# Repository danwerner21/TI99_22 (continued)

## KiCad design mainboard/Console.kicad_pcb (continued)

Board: 2 copper layers, 303 parts (0 on the bottom side), 325 nets, no tracks yet.

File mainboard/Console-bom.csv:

Qty|Reference(s)|Part|Type
---|------------|----|----
30|C1, C9, C11, C57, C63, C70, C71, C72, C73, C74, C75, C76, C77, C78, C80, C81, C82, C84, C85, C86, C87, C88, C89, C90, C91, C92, C93, C94, C95, C96|0.001uF|Capacitor
1|C2|22pF|Capacitor
3|C3, C5, C58|22uF electroyltic|Electrolytic Capacitor
38|C4, C7, C13, C14, C19, C22, C23, C24, C25, C26, C27, C28, C29, C30, C31, C32, C33, C34, C35, C36, C37, C38, C39, C40, C41, C42, C43, C44, C45, C46, C47, C48, C49, C50, C53, C54, C66, C69|0.1uF|Capacitor
1|C6|1uF|Capacitor
8|C8, C12, C51, C62, C64, C65, C79, C83|0.01uF|Capacitor
1|C10|100uF|Capacitor
6|C15, C16, C17, C18, C20, C21,C52,C59|100uF electrolytic|Electrolytic Capacitor
1|C55|12pF|Capacitor
1|C56|56pF|Capacitor
1|C60|220uF electrolytic|Electrolytic Capacitor
1|C61|0.1uF|Capacitor
1|C67|220pF|Capacitor
1|C68|0.022uF|Capacitor
2|CR1, CR4|1N4148|Diode
2|CR2, CR3|1N914B|Diode
1|D1|LED|LED
1|J1|Pin Header 01x02 Male|Pin Header 01x02 Male
1|J2|Pin Header 01x02 Male|Pin Header 01x02 Male
1|J3|Screw Terminal 1x4|Screw Terminal 1x4
1|J4|Pin Header 01x16 Male|Pin Header 01x16 Male
2|J5, J6|Pin Header 01x02 Male|Pin Header 01x02 Male
1|J7|Pin Header 01x02 Male|Pin Header 01x02 Male
1|J8|Pin Header 01x02 Male|Pin Header 01x02 Male
1|J9|DB9 Connector Right Angle Male|DB9 Connector Right Angle Male
1|J10|DB9 Connector Right Angle Male|DB9 Connector Right Angle Male
1|J11|Pin Header 01x18 Male|Pin Header 01x18 Male
1|J12|Pin Header 2x22 Male|Pin Header 2x22 Male
1|J14|36 Pin Edge Connector|CONN EDGE DUAL FMALE 36POS 0.100 spacing
1|J15|Pin Header 02x18 Male|Pin Header 02x18 Male
1|J16|Pin Header 01x03 Male|Pin Header 01x03 Male
1|J17|Pin Header 01x03 Male|Pin Header 01x03 Male
1|L1|0.33uH Inductor|Inductor
9|L2, L3, L4, L12, L13, L14, L15, L16, L17|6.8uH  Inductor|Inductor
4|L5, L6, L7, L11|6.8uH  Inductor|Inductor
1|L8|2- 4.5uH  Inductor|Variable Inductor
1|L9|5.8uH  Inductor|Inductor
1|L10, L18, L19, L20, L21|INDUCTOR (BEAD)|Ferrite Bead
8|Q1, Q3, Q4, Q5, Q6, Q7, Q8, Q9|TIS92 Transistor|Transistor
1|Q2|2N3904  Transistor|Transistor
1|R1|150kohm|Resistor
11|R2, R9, R11, R18, R51, R52, R53, R54, R55, R56, R89|1kohm|Resistor
1|R3|12kohm|Resistor
1|R4|47kohm|Resistor
4|R5, R6, R7, R8|22ohm|Resistor
5|R10, R26, R88, R95, R96|4.7kohm|Resistor
5|R12, R13, R14, R15, R16|1Kohm|Resistor
3|R17, R91, R93|2.2kohm|Resistor
11|R19, R30, R63, R65, R67, R69, R71, R75, R77, R79, R82|470ohm|Resistor
1|R20|270ohm|Resistor
1|R21|1.5kohm|Resistor Network 9 pin
1|R22|361ohm|Resistor
4|R23, R35, R60, R81|5.6kohm|Resistor
4|R24, R27, R80, R83|10ohm|Resistor
1|R25|150ohm|Resistor
1|R28|470kohm|Resistor
1|R29|0ohm|Resistor
2|R31, R33|75ohm|Resistor
1|R32|470ohm|Resistor
11|R34, R40, R41, R42, R43, R44, R45, R46, R47, R48, R100|10kohm|Resistor
2|R36, R58|6.8kohm|Resistor
1|R37|2.2kohm|Resistor
1|R38|200ohm|Resistor
1|R39|120kohm|Resistor
1|R49|39kohm|Resistor
1|R50|6.8kohm|Resistor
1|R57|12kohm|Resistor
1|R59|15ohm|Resistor
2|R61, R62|10kohm|Resistor
2|R64, R72|1kohm|Resistor
2|R66, R76|1.5kohm|Resistor
2|R68, R78|270ohm|Resistor
1|R70|9.1kohm|Resistor
2|R73, R74|220ohm|Resistor
4|R84, R85, R86, R87|62ohm|Resistor
1|R90|3.3kohm|Resistor
4|R92, R94, R97, R99|100ohm|Resistor
1|R98|330ohm|Resistor
1|SW1|Dip Switch 6 pos|Dip Switch 6 pos
1|SW2|Pin Header 01x02 Male|Pin Header 01x02 Male
1|U1|TIM9904|IC
1|U2|TMS9900|IC
4|U3, U15, U20, U21|74LS04|IC
2|U4, U9|74LS32|IC
2|U5, U8|74LS138|IC
1|U6|74LS03|IC
1|U7|74LS08|IC
3|U10, U14, U18|74LS00|IC
2|U11, U40|74LS244|IC
1|U12|74LS373|IC
1|U13|74LS245|IC
1|U16|74LS74|IC
1|U17|74LS194|IC
1|U19|LM7905_TO220|IC
3|U22, U23, U24|TMC0430|IC (optional, replaced by Unicorn Board only known source is from TI/994a console)
3|U25, U26, U33|HM62256BLP|IC
2|U27, U28|27C64|IC
1|U29|SN76489|IC
1|U30|TMS9918|IC
3|U31, U32, U34|74LS574|IC
1|U35|TMS9901|IC
1|U36|RC4558|IC
1|U37|74LS156|IC
2|U38, U39|TIL119|IC
2|U41, U42|74LS367|IC
1|U43|74LS379|IC
1|U44|27C010|IC
1|Y1|48.000 MHz Crystal|Crystal
1|Y2|10.7MHz Crystal|Crystal

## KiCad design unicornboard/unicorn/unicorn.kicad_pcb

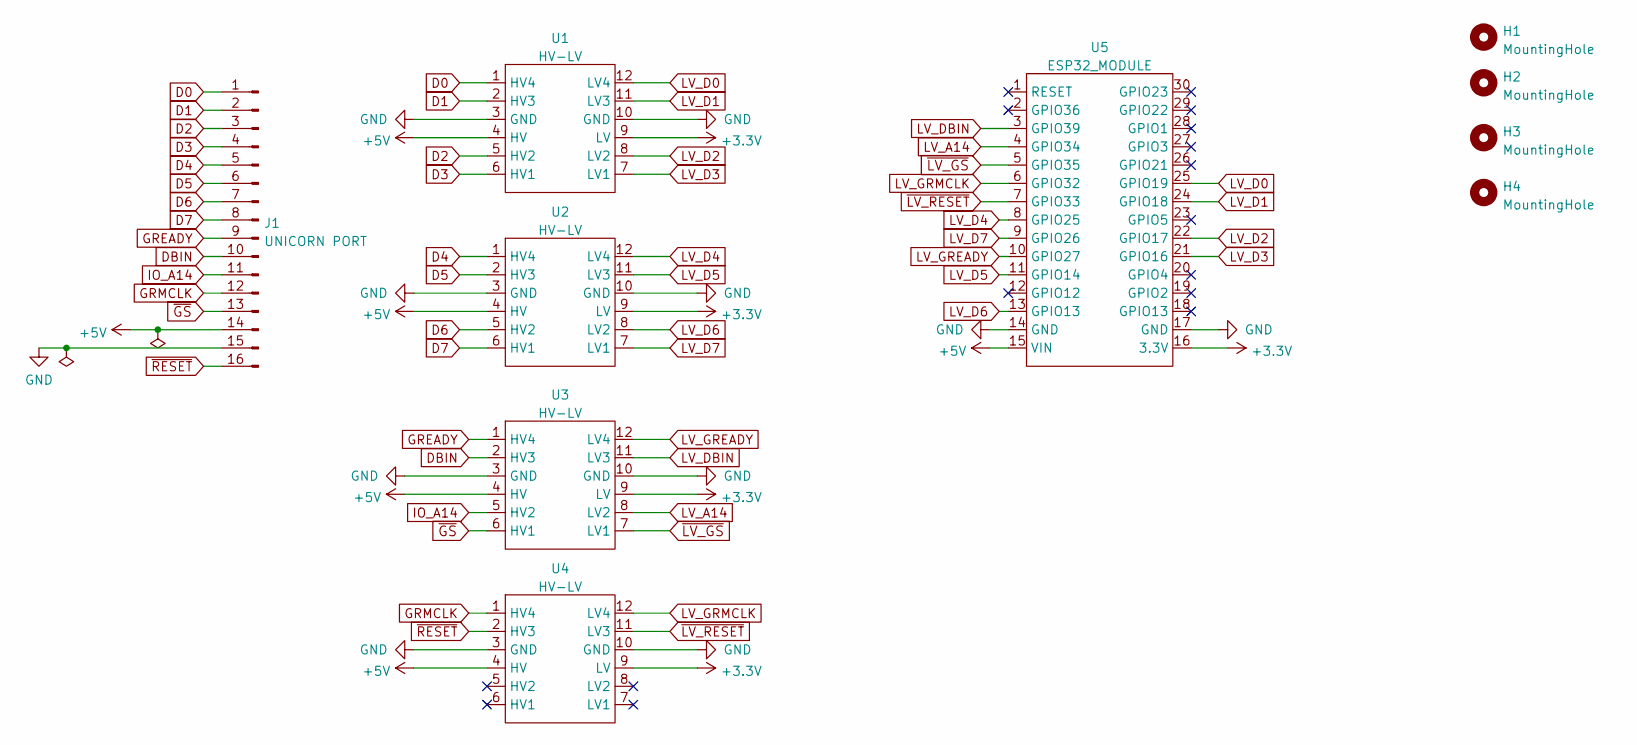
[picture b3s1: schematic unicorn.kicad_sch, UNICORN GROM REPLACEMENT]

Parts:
H1, H2, H3, H4: MountingHole; MountingHole_3.2mm_M3
J1: UNICORN PORT; PinHeader_1x16_P2.54mm_Vertical
U1, U2, U3, U4: HV-LV
U5: ESP32_MODULE; ESP32_DEVKIT_30

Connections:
+3.3V: U1.9 (LV), U2.9 (LV), U3.9 (LV), U4.9 (LV), U5.16 (3.3V)
+5V: J1.14, U1.4 (HV), U2.4 (HV), U3.4 (HV), U4.4 (HV), U5.15 (VIN)
D0: J1.1, U1.1 (HV4)
D1: J1.2, U1.2 (HV3)
D2: J1.3, U1.5 (HV2)
D3: J1.4, U1.6 (HV1)
D4: J1.5, U2.1 (HV4)
D5: J1.6, U2.2 (HV3)
D6: J1.7, U2.5 (HV2)
D7: J1.8, U2.6 (HV1)
DBIN: J1.10, U3.2 (HV3)
GND: J1.15, U1.3 (GND), U1.10 (GND), U2.3 (GND), U2.10 (GND), U3.3 (GND), U3.10 (GND), U4.3 (GND), U4.10 (GND), U5.14 (GND), U5.17 (GND)
GREADY: J1.9, U3.1 (HV4)
GRMCLK: J1.12, U4.1 (HV4)
IO_A14: J1.11, U3.5 (HV2)
LV_A14: U3.8 (LV2), U5.4 (GPIO34)
LV_D0: U1.12 (LV4), U5.25 (GPIO19)
LV_D1: U1.11 (LV3), U5.24 (GPIO18)
LV_D2: U1.8 (LV2), U5.22 (GPIO17)
LV_D3: U1.7 (LV1), U5.21 (GPIO16)
LV_D4: U2.12 (LV4), U5.8 (GPIO25)
LV_D5: U2.11 (LV3), U5.11 (GPIO14)
LV_D6: U2.8 (LV2), U5.13 (GPIO13)
LV_D7: U2.7 (LV1), U5.9 (GPIO26)
LV_DBIN: U3.11 (LV3), U5.3 (GPIO39)
LV_GREADY: U3.12 (LV4), U5.10 (GPIO27)
LV_GRMCLK: U4.12 (LV4), U5.6 (GPIO32)
~GS: J1.13, U3.6 (HV1)
~LV_GS: U3.7 (LV1), U5.5 (GPIO35)
~LV_RESET: U4.11 (LV3), U5.7 (GPIO33)
~RESET: J1.16, U4.2 (HV3)

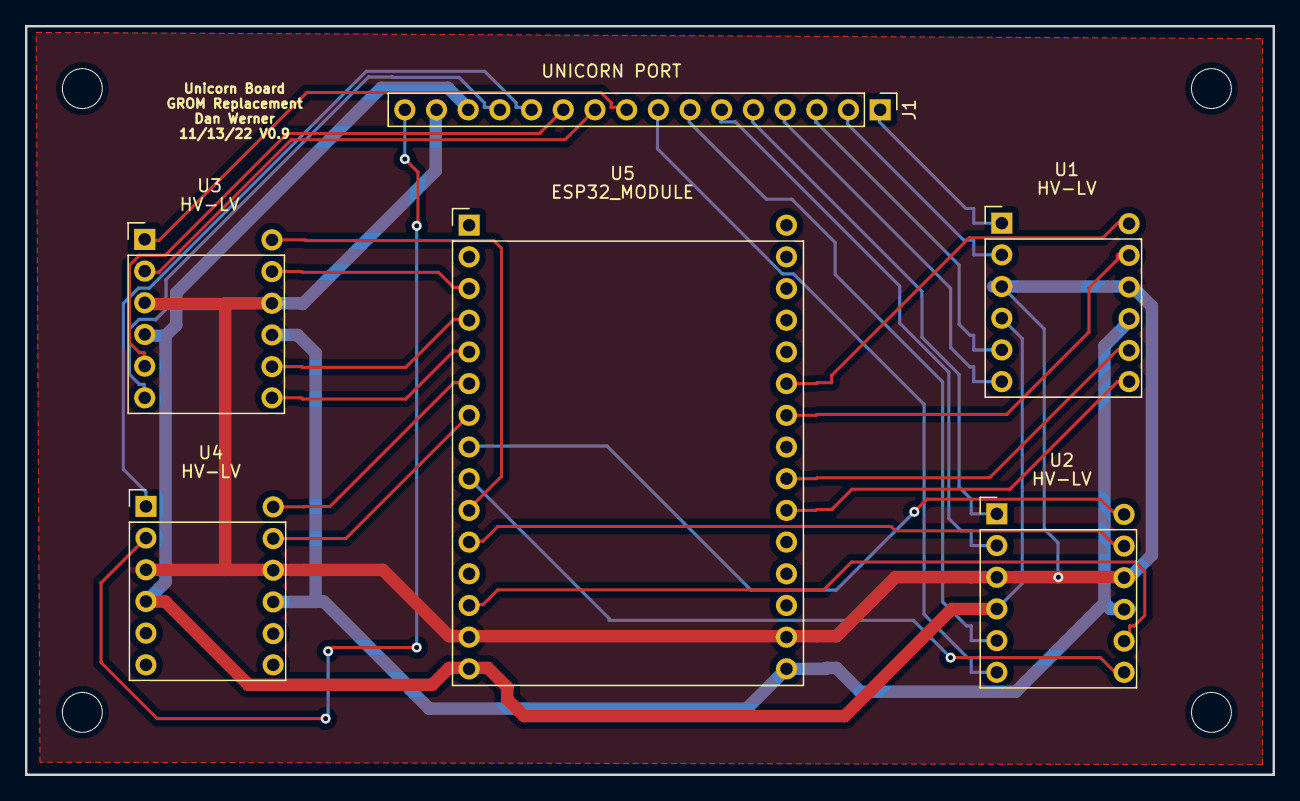
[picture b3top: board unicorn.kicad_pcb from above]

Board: 2 copper layers, 100.0 x 60.0 mm, 10 parts (0 on the bottom side), 31 nets.

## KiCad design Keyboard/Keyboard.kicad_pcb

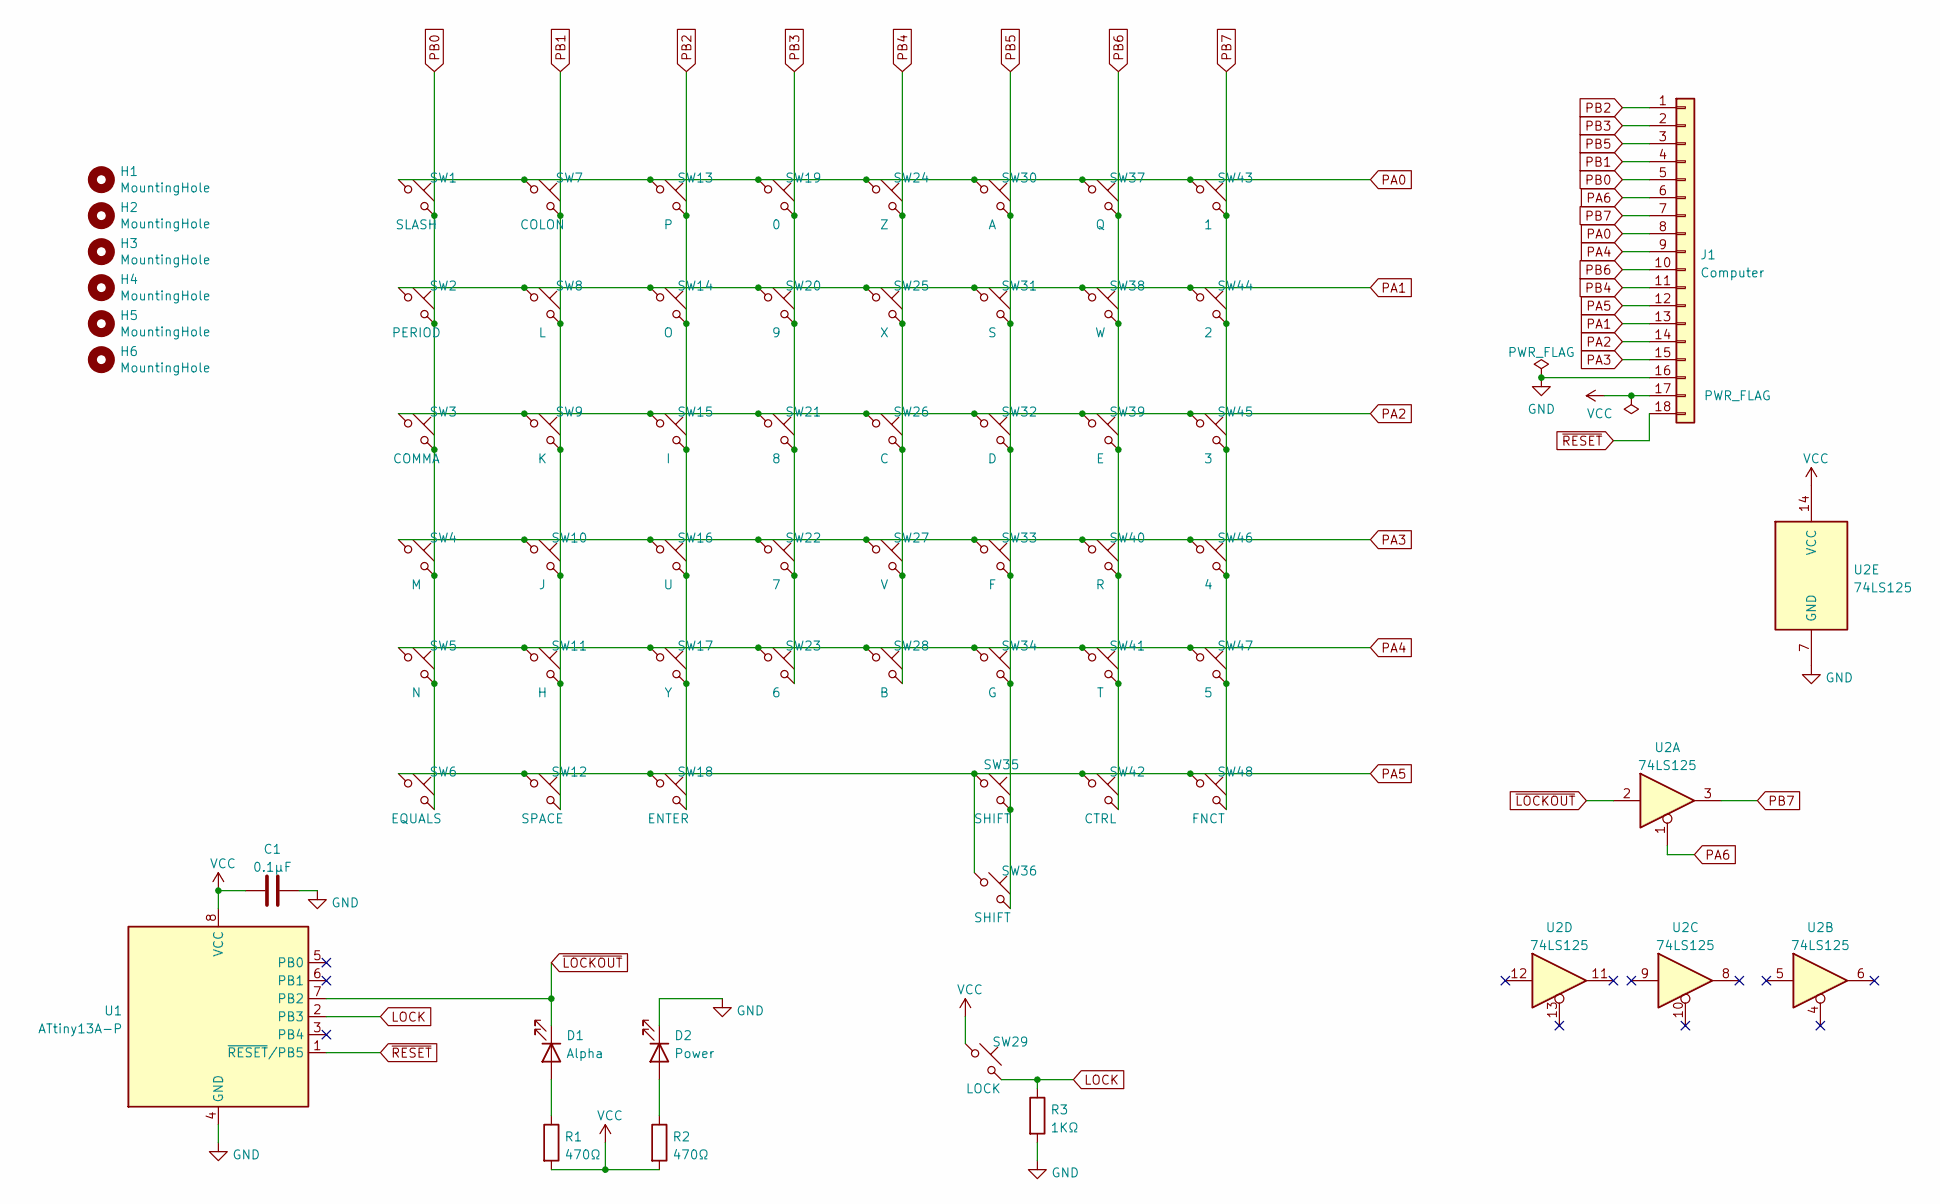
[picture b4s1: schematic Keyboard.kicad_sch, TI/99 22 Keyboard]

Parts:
C1: 0.1µF; C_Disc_D7.0mm_W2.5mm_P5.00mm
D1: Alpha; LED_D3.0mm
D2: Power; LED_D3.0mm
H1, H2, H3, H4, H5, H6: MountingHole; MountingHole_3.2mm_M3_Pad
J1: Computer; PinHeader_1x18_P2.54mm_Vertical
R1, R2: 470Ω; R_Axial_DIN0207_L6.3mm_D2.5mm_P7.62mm_Horizontal
R3: 1KΩ; R_Axial_DIN0207_L6.3mm_D2.5mm_P7.62mm_Horizontal
SW1: SLASH; CHERRY_PCB_100H
SW2: PERIOD; CHERRY_PCB_100H
SW3: COMMA; CHERRY_PCB_100H
SW4: M; CHERRY_PCB_100H
SW5: N; CHERRY_PCB_100H
SW6: EQUALS; CHERRY_PCB_100H
SW7: COLON; CHERRY_PCB_100H
SW8: L; CHERRY_PCB_100H
SW9: K; CHERRY_PCB_100H
SW10: J; CHERRY_PCB_100H
SW11: H; CHERRY_PCB_100H
SW12: SPACE; CHERRY_PCB_625H
SW13: P; CHERRY_PCB_100H
SW14: O; CHERRY_PCB_100H
SW15: I; CHERRY_PCB_100H
SW16: U; CHERRY_PCB_100H
SW17: Y; CHERRY_PCB_100H
SW18: ENTER; CHERRY_PCB_225H
SW19: 0; CHERRY_PCB_100H
SW20: 9; CHERRY_PCB_100H
SW21: 8; CHERRY_PCB_100H
SW22: 7; CHERRY_PCB_100H
SW23: 6; CHERRY_PCB_100H
SW24: Z; CHERRY_PCB_100H
SW25: X; CHERRY_PCB_100H
SW26: C; CHERRY_PCB_100H
SW27: V; CHERRY_PCB_100H
SW28: B; CHERRY_PCB_100H
SW29: LOCK; SW_Cherry_MX_1.75u_PCB
SW30: A; CHERRY_PCB_100H
SW31: S; CHERRY_PCB_100H
SW32: D; CHERRY_PCB_100H
SW33: F; CHERRY_PCB_100H
SW34: G; CHERRY_PCB_100H
SW35: SHIFT; CHERRY_PCB_275H
SW36: SHIFT; CHERRY_PCB_225H
SW37: Q; CHERRY_PCB_100H
SW38: W; CHERRY_PCB_100H
SW39: E; CHERRY_PCB_100H
SW40: R; CHERRY_PCB_100H
SW41: T; CHERRY_PCB_100H
SW42: CTRL; SW_Cherry_MX_1.25u_PCB
SW43: 1; CHERRY_PCB_100H
SW44: 2; CHERRY_PCB_100H
SW45: 3; CHERRY_PCB_100H
SW46: 4; CHERRY_PCB_100H
SW47: 5; CHERRY_PCB_100H
SW48: FNCT; SW_Cherry_MX_1.25u_PCB
U1: ATtiny13A-P; DIP-8_W7.62mm_LongPads
U2: 74LS125; DIP-14_W7.62mm_Socket_LongPads

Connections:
GND: C1.2, D2.1 (K), J1.16, R3.2, U1.4 (GND), U2.7 (GND)
LOCK: R3.1, SW29.2, U1.2 (PB3)
unnamed: D1.2 (A), R1.1
unnamed: D2.2 (A), R2.1
PA0: J1.8, SW1.1, SW7.1, SW13.1, SW19.1, SW24.1, SW30.1, SW37.1, SW43.1
PA1: J1.13, SW2.1, SW8.1, SW14.1, SW20.1, SW25.1, SW31.1, SW38.1, SW44.1
PA2: J1.14, SW3.1, SW9.1, SW15.1, SW21.1, SW26.1, SW32.1, SW39.1, SW45.1
PA3: J1.15, SW4.1, SW10.1, SW16.1, SW22.1, SW27.1, SW33.1, SW40.1, SW46.1
PA4: J1.9, SW5.1, SW11.1, SW17.1, SW23.1, SW28.1, SW34.1, SW41.1, SW47.1
PA5: J1.12, SW6.1, SW12.1, SW18.1, SW35.1, SW36.1, SW42.1, SW48.1
PA6: J1.6, U2.1
PB0: J1.5, SW1.2, SW2.2, SW3.2, SW4.2, SW5.2, SW6.2
PB1: J1.4, SW7.2, SW8.2, SW9.2, SW10.2, SW11.2, SW12.2
PB2: J1.1, SW13.2, SW14.2, SW15.2, SW16.2, SW17.2, SW18.2
PB3: J1.2, SW19.2, SW20.2, SW21.2, SW22.2, SW23.2
PB4: J1.11, SW24.2, SW25.2, SW26.2, SW27.2, SW28.2
PB5: J1.3, SW30.2, SW31.2, SW32.2, SW33.2, SW34.2, SW35.2, SW36.2
PB6: J1.10, SW37.2, SW38.2, SW39.2, SW40.2, SW41.2, SW42.2
PB7: J1.7, SW43.2, SW44.2, SW45.2, SW46.2, SW47.2, SW48.2, U2.3
VCC: C1.1, J1.17, R1.2, R2.2, SW29.1, U1.8 (VCC), U2.14 (VCC)
~LOCKOUT: D1.1 (K), U1.7 (PB2), U2.2
~RESET: J1.18, U1.1 (~RESET/PB5)

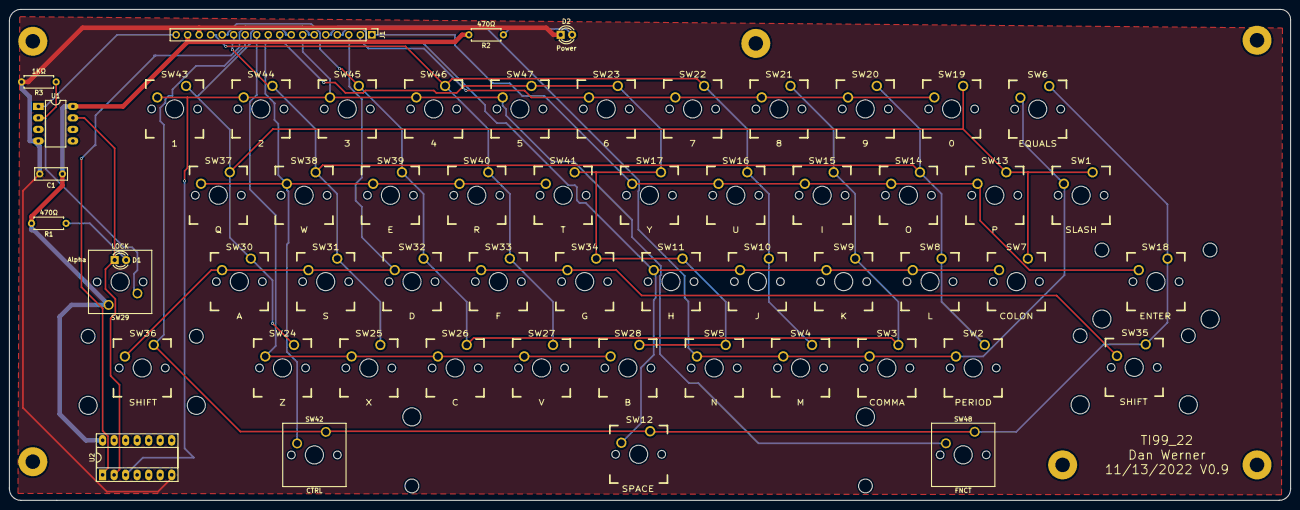
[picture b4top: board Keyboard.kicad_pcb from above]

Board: 2 copper layers, 282.7 x 108.3 mm, 63 parts (0 on the bottom side), 22 nets.

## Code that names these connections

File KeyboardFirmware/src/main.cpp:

#include <Arduino.h>

//========================================================================
// Hardwiring the ATtiny85
//========================================================================
/*
                             ____  ____
               /RESET (PB5) -|   \/   |- (Vcc)
                 LOCK (PB3) -|        |- (PB2) CAPS LED
                   nc (PB4) -|        |- (PB1) MATRIX PA6 (OUT)
                      (GND) -|________|- (PB0) MATRIX PB7 (IN)

*/

static int capslock = 0;
static int buttonState = LOW; //this variable tracks the state of the button, low if not pressed, high if pressed
static unsigned long lastDebounceTime = 0;  // the last time the output pin was toggled
static unsigned long debounceDelay = 50;    // the debounce time; increase if the output flickers

void setup()
{
  pinMode(3, INPUT);
  pinMode(2, OUTPUT);
  digitalWrite(2, HIGH);
}

void loop() {
  buttonState = digitalRead(3);

  if ( (millis() - lastDebounceTime) > debounceDelay) {
    if ( (buttonState == HIGH) && (capslock == 0) ) {
      digitalWrite(2, LOW); //turn LED on
      capslock=1;
      lastDebounceTime = millis(); //set the current time
    }
    else if ( (buttonState == HIGH) && (capslock != 0) ) {
      digitalWrite(2, HIGH); //turn LED off
      capslock=0;
      lastDebounceTime = millis(); //set the current time
    }
  }
}

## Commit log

2022-06-30 PCB routed
2022-10-16 unicorn work
2022-10-17 Doc Updates
2022-10-23 unicorn firmware working
2022-10-23 update documentation
2022-10-25 PCB correction
2022-10-25 trim cart riser
2022-10-25 rework IO Riser
2022-11-05 Shrink PCB
2022-11-14 hardware updates
2022-11-20 Add BOM
2022-11-20 PCB updates
2022-11-20 update STLs
2022-12-13 PCB cleanup
2022-12-25 PCB power fix
2022-12-27 PCB rework
2022-12-27 PCB BOM
2023-01-09 3d models
2023-01-21 PCB 0.96
2023-03-30 case work
2023-07-13 Correct PCB PDF
2024-09-03 readme update
2024-10-05 Update docs, add keyboard firmware
